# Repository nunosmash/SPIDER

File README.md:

[README.md](https://github.com/user-attachments/files/26697123/README.md)
# SPIDER

**BLE MIDI gateway** — bridge **Bluetooth LE MIDI** controllers to **USB MIDI** and **DIN MIDI**, with up to **three** simultaneous BLE devices, **fixed slot routing**, and **HOST** / **CLIENT** roles for stage and DAWless setups.

Part of the **Ash Sound Works** custom tools for live and studio — by sound artist and producer **Ash (Ahn Sunghoon)** · [GitHub](https://github.com/nunosmash) / 
[Manual](http://ashsoundworks.com/spider-manual.html)

---

## Why SPIDER?

Running cables across a crowded **pedalboard** or needing **remote** control for other players is awkward. SPIDER was built around **BLE MIDI** on a dedicated **nRF52840** radio (e.g. **nice!nano** class hardware): low power, battery-friendly, and focused on **wireless MIDI** rather than sharing the stack with a desktop OS BLE stack.

---

## Key features

- Up to **3** BLE MIDI controllers connected at once  
- **USB MIDI** via **TinyUSB** — **3 independent virtual MIDI ports** (one per slot)  
- **DIN MIDI** — **Slot 0** routes to DIN when appropriate (see routing below)  
- **7.5 ms** BLE connection interval class; low-latency slot timing (~**5 ms** average response in typical use)  
- **TX power** auto-adjust **0 ~ +8 dBm** from **RSSI**  
- **Battery monitoring** for the unit and connected gear (where supported)  
- **OLED** UI with power-save brightness (USB vs battery profiles)  
- **HOST** and **CLIENT** modes  

---

## Routing architecture

| Role | Behavior (summary) |
|------|---------------------|
| **Slot 0 (master)** | USB ↔ BLE ↔ DIN MIDI |
| **Slots 1–2** | USB ↔ BLE |
| **Port pinning** | Each slot stores **MAC + name** so devices **always** map to the same slot regardless of power-on order |

### HOST mode

- **USB data connected:** BLE → **USB MIDI** (DIN blocked for that path per firmware logic)  
- **No USB data:** Slot 0 → **DIN MIDI** output  
- Slot management: **RESCAN**, **CLEAR SLOT**, auto-reconnect  

### CLIENT mode

- Uses **one slot** to join a host  
- Remembers first trusted host **MAC** (save window ~30 s on first connect); optional **block** for unwanted devices  

---

## OLED / status (summary)

- Top line: **LOW BAT**, **WEAK SIG**, **M** (DIN active), TX power hints  
- Per slot: **EMPTY** / **OFFLINE** / **CONNECTED**  
- MIDI traffic: ▽ in / △ out  
- Battery: **%** or **N/A** if unknown  

### Antenna bars (signal guide)

- **6–4 bars** — best; within ~**10 m** reliable  
- **3 bars** — stable for normal use  
- **≤2 bars** — TX power ramps up; maintain connection  
- **0 bars** — unreliable; move closer  

**Tip:** Keep **3+ bars** within ~**10 m** for dependable live use.

---

## Ableton Live (quick setup)

**Preferences → Link / Tempo / MIDI**

- **Input:** SPIDER MIDI **Port 1, 2, 3** → **Track** ON, **Remote** ON as needed  
- **Output:** enable if you send MIDI back to wireless gear  

| Slot | USB MIDI port |
|------|----------------|
| SLOT 1 | Port 1 |
| SLOT 2 | Port 2 |
| SLOT 3 | Port 3 |

---

## Sync calibration

BLE adds variable delay; align with audio using **Track Delay** like any MIDI path. Many setups start around **−10 ms ~ −20 ms** (often **−18 ms**) and refine by recording MIDI out + external audio and matching to the grid.

---

## Firmware update

1. Connect SPIDER over **USB**.  
2. Hold the **encoder button** for **5+ seconds** to enter firmware update mode (**USB mass storage** / removable drive).  
3. Copy the released firmware file to the mounted drive; device updates and reboots.  

(Exact filename and format follow your published release notes.)

---

## Use cases

- **Band live** — multiple wireless controllers into one DAW reliably  
- **DAWless** — Slot 0 → hardware synths via DIN  
- **Multi-computer** — advanced MIDI routing between several hosts (see full manual)  

---

## Repository contents

Depending on branch or release:

- Firmware (Zephyr / Arduino / etc. — match your repo)  
- Schematics / PCB / case files  
- Build and flash instructions  

Full wiring, menus, and edge cases: **`spider-manual.html`** in the Ash Sound Works bundle.

---

## Hardware Specifications (BOM)

| Category | Component Description | Qty |
| :--- | :--- | :---: |
| **MCU** | nRF52840 (nice!nano v2.0 SuperMini) | 1 |
| **Display** | 0.91" OLED Module (128x64) | 1 |
| **Optocoupler** | 6N138 High-Speed Optocoupler | 1 |
| **Diode** | 1N4001 Rectifier Diode | 1 |
| **Capacitor** | 100μF Electrolytic Capacitor | 1 |
| **Input** | EC11 Rotary Encoder w/ Push Switch | 1 |
| **Connectors** | PJ-320A 3.5mm Stereo Jack | 2 |
| **Power** | SS-12F23 Slide Switch | 1 |
| **Resistors** | 220Ω (x2), 330Ω (x2), 150Ω, 1kΩ, 4.7kΩ, 10Ω, 30Ω | 9 |

## Documentation

- Full manual: `spider-manual.html`  
- Other projects: [github.com/nunosmash](https://github.com/nunosmash)

---

## Disclaimer

- **BLE** performance depends on environment, antennas, and interference — always **test** before a show.  
- Verify **DIN polarity** (Type A/B) when connecting legacy MIDI gear.  
- DIY: observe battery and USB power safety.

---

## License

See the `LICENSE` file in the repository root.

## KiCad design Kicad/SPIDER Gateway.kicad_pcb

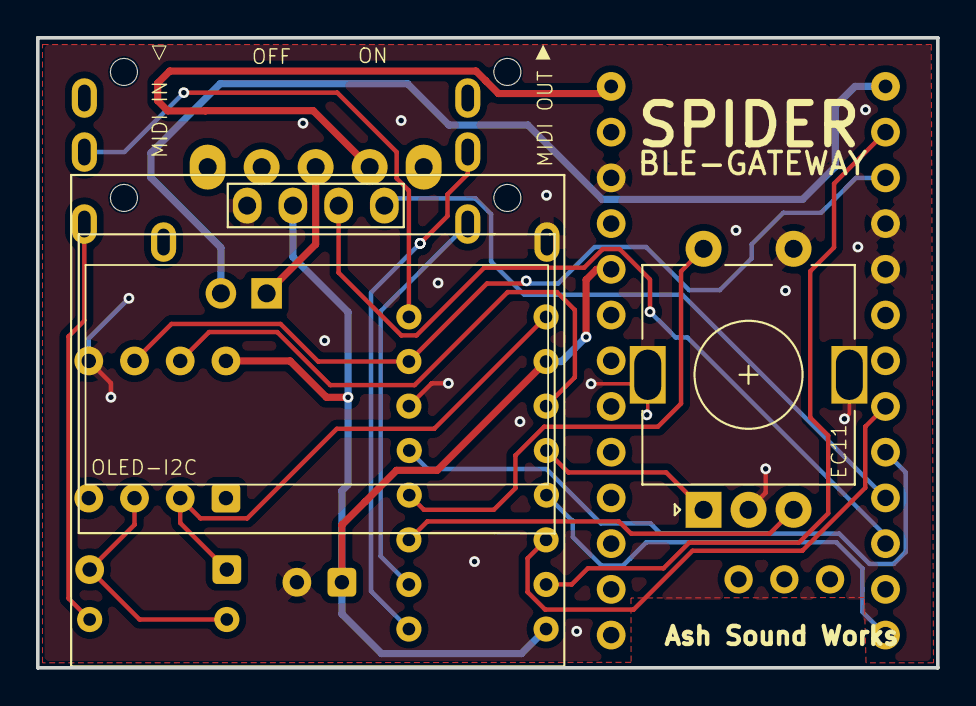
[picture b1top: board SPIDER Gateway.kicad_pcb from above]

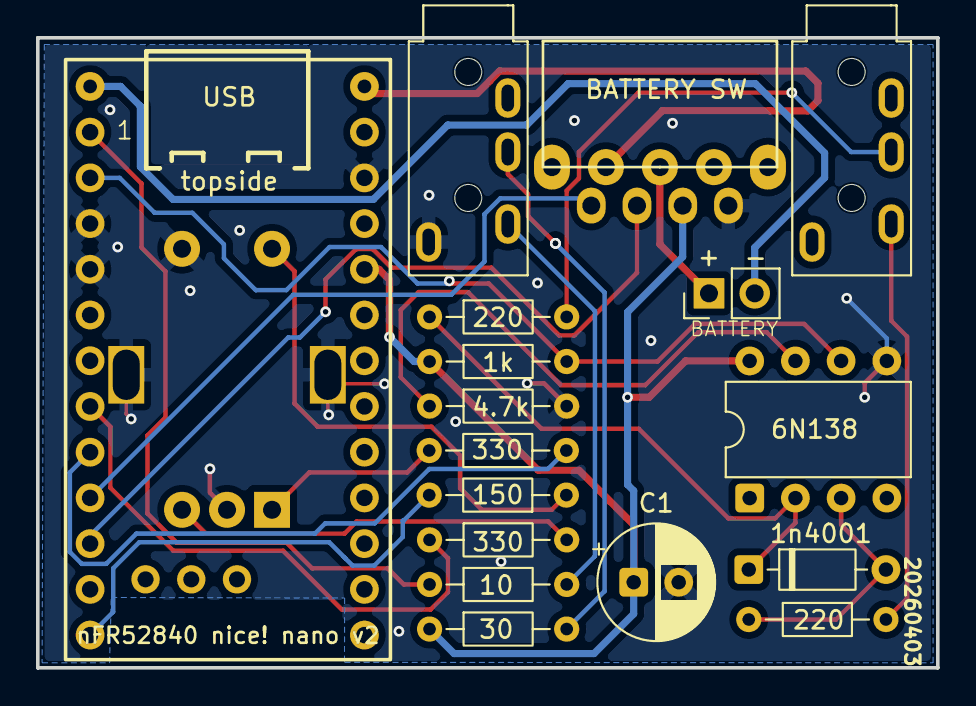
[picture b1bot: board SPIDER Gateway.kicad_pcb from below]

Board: 2 copper layers, 50.0 x 35.0 mm, 19 parts (17 on the bottom side), 22 nets.

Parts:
1n4001: 1n4001; D_DO-35_SOD27_P7.62mm_Horizontal
C1: 100uF; CP_Radial_D6.3mm_P2.50mm
Enc5: EC11; RotaryEncoder_Alps_EC11E-Switch_Vertical_H20mm
J1: BATTERY; PinHeader_1x02_P2.54mm_Vertical
J2: MIDI IN ◁; PJ-320A
J3: MIDI OUT; PJ-320A
R4, R8: 220; R_Axial_DIN0204_L3.6mm_D1.6mm_P7.62mm_Horizontal
R5: 150; R_Axial_DIN0204_L3.6mm_D1.6mm_P7.62mm_Horizontal
R9: 1k; R_Axial_DIN0204_L3.6mm_D1.6mm_P7.62mm_Horizontal
R10: 4.7k; R_Axial_DIN0204_L3.6mm_D1.6mm_P7.62mm_Horizontal
R13, R14: 330; R_Axial_DIN0204_L3.6mm_D1.6mm_P7.62mm_Horizontal
R19: 10; R_Axial_DIN0204_L3.6mm_D1.6mm_P7.62mm_Horizontal
R20: 30; R_Axial_DIN0204_L3.6mm_D1.6mm_P7.62mm_Horizontal
SW1: SW_SPDT; SS-12F23
U1: nFR52840 nice! nano v2; SuperMini NRF52840
U2: 6N138; DIP-8_W7.62mm
U3: OLED-I2C; 128x64OLED

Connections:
3.3V VCC: C1.1, R9.1, R20.1, U1.16 (3V3), U2.8 (VCC), U3.2 (VCC)
BATTERY +: J1.1, SW1.2 (B)
BATTERY -: J1.2, U1.28 (GND)
ENC A: R13.1, U1.8 (P0.24)
ENC B: R14.1, U1.7 (P0.22)
GND: C1.2, Enc5.C, Enc5.MP, Enc5.S1, J3.S, R10.2, U1.3 (GND), U1.4 (GND), U1.14 (GND), U2.5 (GND), U3.1 (GND)
unnamed: 1n4001.2 (A), R4.1, U2.3 (C2)
unnamed: 1n4001.1 (K), R8.1, U2.2 (C1)
unnamed: Enc5.A, R13.2
unnamed: Enc5.B, R14.2
unnamed: Enc5.S2, R5.1
unnamed: J2.R1, R8.2
unnamed: J2.T, R4.2
unnamed: J3.R1, R20.2
unnamed: J3.T, R19.2
unnamed: SW1.3 (C), U1.29 (BAT+)
unnamed: R10.1, U2.7 (VO1)
RX: R9.2, U1.2 (P0.08), U2.6 (VO2)
SCK: U1.10 (P0.11), U3.3 (SCL)
SDA: U1.9 (P1.00), U3.4 (SDA)
SW: R5.2, U1.12 (P1.06-LF)
TX: R19.1, U1.1 (P0.06)

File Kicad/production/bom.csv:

Designator,Footprint,Quantity,Value,LCSC Part #
1N4001,D_DO-35_SOD27_P7.62mm_Horizontal,1,1n4001,
C1,CP_Radial_D6.3mm_P2.50mm,1,100uF,
ENC5,RotaryEncoder_Alps_EC11E-Switch_Vertical_H20mm,1,EC11,
J1,PinHeader_1x02_P2.54mm_Vertical,1,BATTERY,
J2,PJ-320A,1,MIDI IN ◁ ,
J3,PJ-320A,1,MIDI OUT,
R10,R_Axial_DIN0204_L3.6mm_D1.6mm_P7.62mm_Horizontal,1,4.7k,
"R13, R14",R_Axial_DIN0204_L3.6mm_D1.6mm_P7.62mm_Horizontal,2,330,
R19,R_Axial_DIN0204_L3.6mm_D1.6mm_P7.62mm_Horizontal,1,10,
R20,R_Axial_DIN0204_L3.6mm_D1.6mm_P7.62mm_Horizontal,1,30,
"R4, R8",R_Axial_DIN0204_L3.6mm_D1.6mm_P7.62mm_Horizontal,2,220,
R5,R_Axial_DIN0204_L3.6mm_D1.6mm_P7.62mm_Horizontal,1,150,
R9,R_Axial_DIN0204_L3.6mm_D1.6mm_P7.62mm_Horizontal,1,1k,
SW1,SS-12F23,1,SW_SPDT,
U2,DIP-8_W7.62mm,1,6N138,
U3,128x64OLED,1,OLED-I2C,

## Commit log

2026-04-27 Add hardware specifications to README
    Added hardware specifications table with components and quantities.
2026-04-27 Add assembly video link to README
    Added a link to the assembly video in the documentation section.
